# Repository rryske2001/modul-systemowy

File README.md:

# Moduł Systemowy HD44780 LCD Driver & PCB Adapter Collection

## 📖 O projekcie

Niniejsze repozytorium zawiera kompleksowe rozwiązanie dla obsługi popularnych wyświetlaczy znakowych LCD opartych na sterowniku **HD44780**. Projekt składa się z dwóch głównych filarów:
1.  **Warstwa sprzętowa:** Projekty płytek drukowanych (PCB) wykonane w środowisku **KiCad**, służące jako adaptery i moduły interfejsowe dla wyświetlaczy 16x2, 20x4 oraz 40x2.
2.  **Warstwa programowa:** Biblioteki sterowników napisane w języku C, obsługujące różne tryby komunikacji (I2C, 4-bit, 8-bit) ze szczególnym naciskiem na optymalizację (odczyt flagi zajętości - Busy Flag).

---

## 🛠️ Funkcjonalności

### 🔌 Hardware (Projekty PCB)
Projekty płytek zostały przygotowane w programie **KiCad**. Repozytorium zawiera pliki produkcyjne oraz źródłowe dla kilku wariantów:
* **Wersje jedno- i dwuwarstwowe:** Dostosowane do różnych metod produkcji (domowe trawienie vs profesjonalna produkcja).
* **Uniwersalność:** Obsługa popularnych formatów wyświetlaczy: 16x2, 20x4 oraz 40x2.
* **Adaptery I2C:** Projekty integrujące ekspandery portów (np. PCF8574) bezpośrednio z wyświetlaczem, co redukuje liczbę wymaganych pinów mikrokontrolera.

### 💻 Software (Sterowniki)
Kod źródłowy zawiera implementację sterowników w różnych konfiguracjach sprzętowych:
* **Obsługa I2C:** Sterowanie poprzez ekspander (PCF8574), idealne dla systemów z ograniczoną liczbą GPIO.
* **Tryb równoległy (4-bit i 8-bit):** Klasyczne sterowanie bezpośrednie.
* **Busy Flag Check:** Zaimplementowany mechanizm odczytu flagi zajętości sterownika HD44780. Pozwala to na uniknięcie sztywnych opóźnień (`delay`), co znacząco zwiększa wydajność całego systemu wbudowanego.
* **Interfejs szeregowy:** Alternatywne metody komunikacji.

---

## 📂 Struktura Repozytorium

Poniżej znajduje się opis zawartości kluczowych katalogów:

### Projekty KiCad
* `/Wersja_z_I2C_8bit_...` - Projekt dwuwarstwowej płytki z integracją I2C.
* `/Wersja_16x2_20x4_...` - Uniwersalna płytka jednowarstwowa dla standardowych wyświetlaczy.
* `/wersja_ostateczna_wyswietlacz_pcf_v1` - Finalna wersja adaptera z układem PCF.

### Kod Źródłowy
* `/wyswietlacz_interfejs_4_bit_BusyFlag` - Sterownik 4-bitowy z odczytem BF.
* `/testy_z_ekspanderem_pcf` - Kod testowy dla komunikacji I2C.
* `/wyswietlacz_interfejs_8_bit` - Podstawowa obsługa w trybie 8-bitowym.

---

## 🔧 Technologie i Narzędzia

* **Projektowanie PCB:** KiCad EDA
* **Język programowania:** C (Embedded)
* **Hardware:** Wyświetlacze HD44780, Ekspandery PCF8574
* **Protokoły:** I2C, Parallel Interface

---

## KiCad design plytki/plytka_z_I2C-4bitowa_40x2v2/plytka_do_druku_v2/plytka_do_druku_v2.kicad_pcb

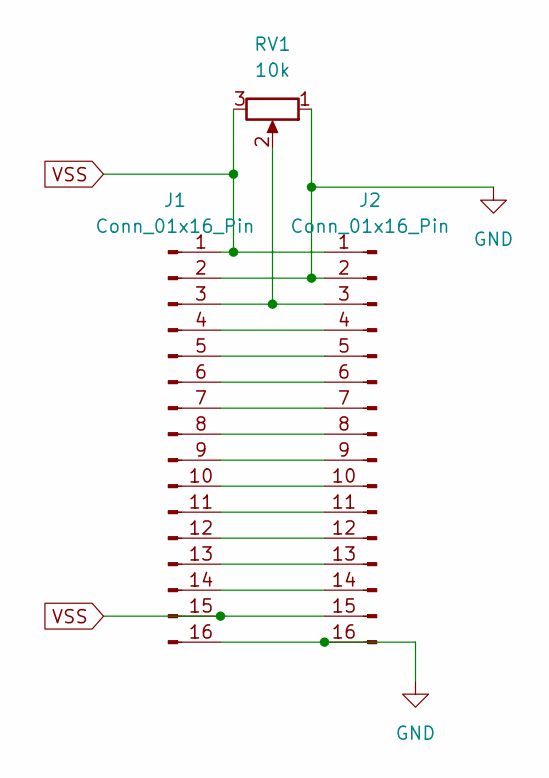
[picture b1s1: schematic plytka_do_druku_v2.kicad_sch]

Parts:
J1: Conn_01x16_Pin; PinSocket_1x16_P2.54mm_Vertical
J2: Conn_01x16_Pin; waski
RV1: 10k; Potentiometer_Alps_RK09Y11_Single_Horizontal

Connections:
GND: J1.2, J1.16, J2.2, J2.16, RV1.1
unnamed: J1.3, J2.3, RV1.2
unnamed: J1.4, J2.4
unnamed: J1.5, J2.5
unnamed: J1.6, J2.6
unnamed: J1.7, J2.7
unnamed: J1.8, J2.8
unnamed: J1.9, J2.9
unnamed: J1.10, J2.10
unnamed: J1.11, J2.11
unnamed: J1.12, J2.12
unnamed: J1.13, J2.13
unnamed: J1.14, J2.14
VSS: J1.1, J1.15, J2.1, J2.15, RV1.3

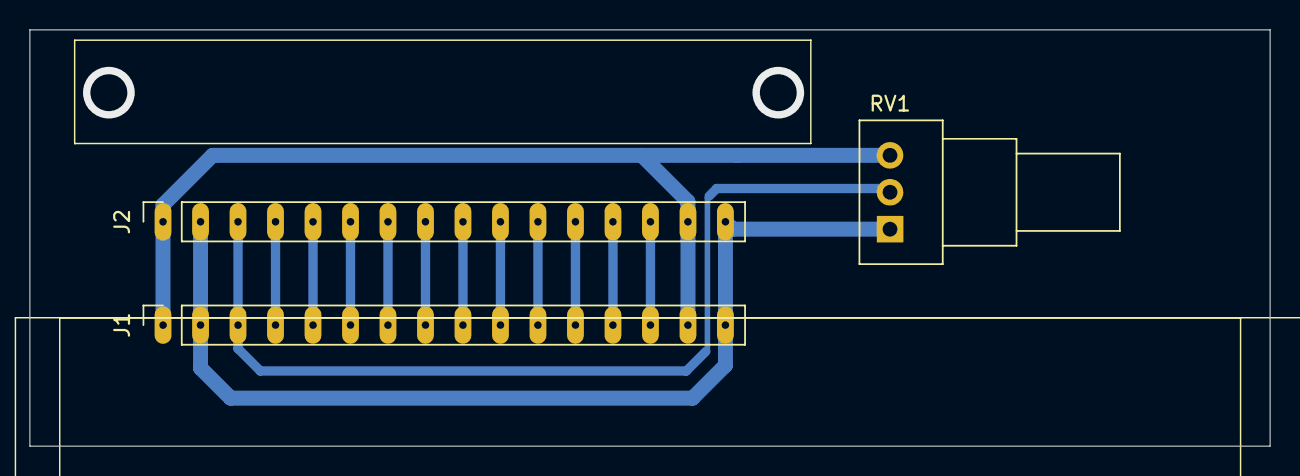
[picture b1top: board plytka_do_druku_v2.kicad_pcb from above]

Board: 2 copper layers, 84.0 x 28.2 mm, 3 parts (0 on the bottom side), 14 nets.

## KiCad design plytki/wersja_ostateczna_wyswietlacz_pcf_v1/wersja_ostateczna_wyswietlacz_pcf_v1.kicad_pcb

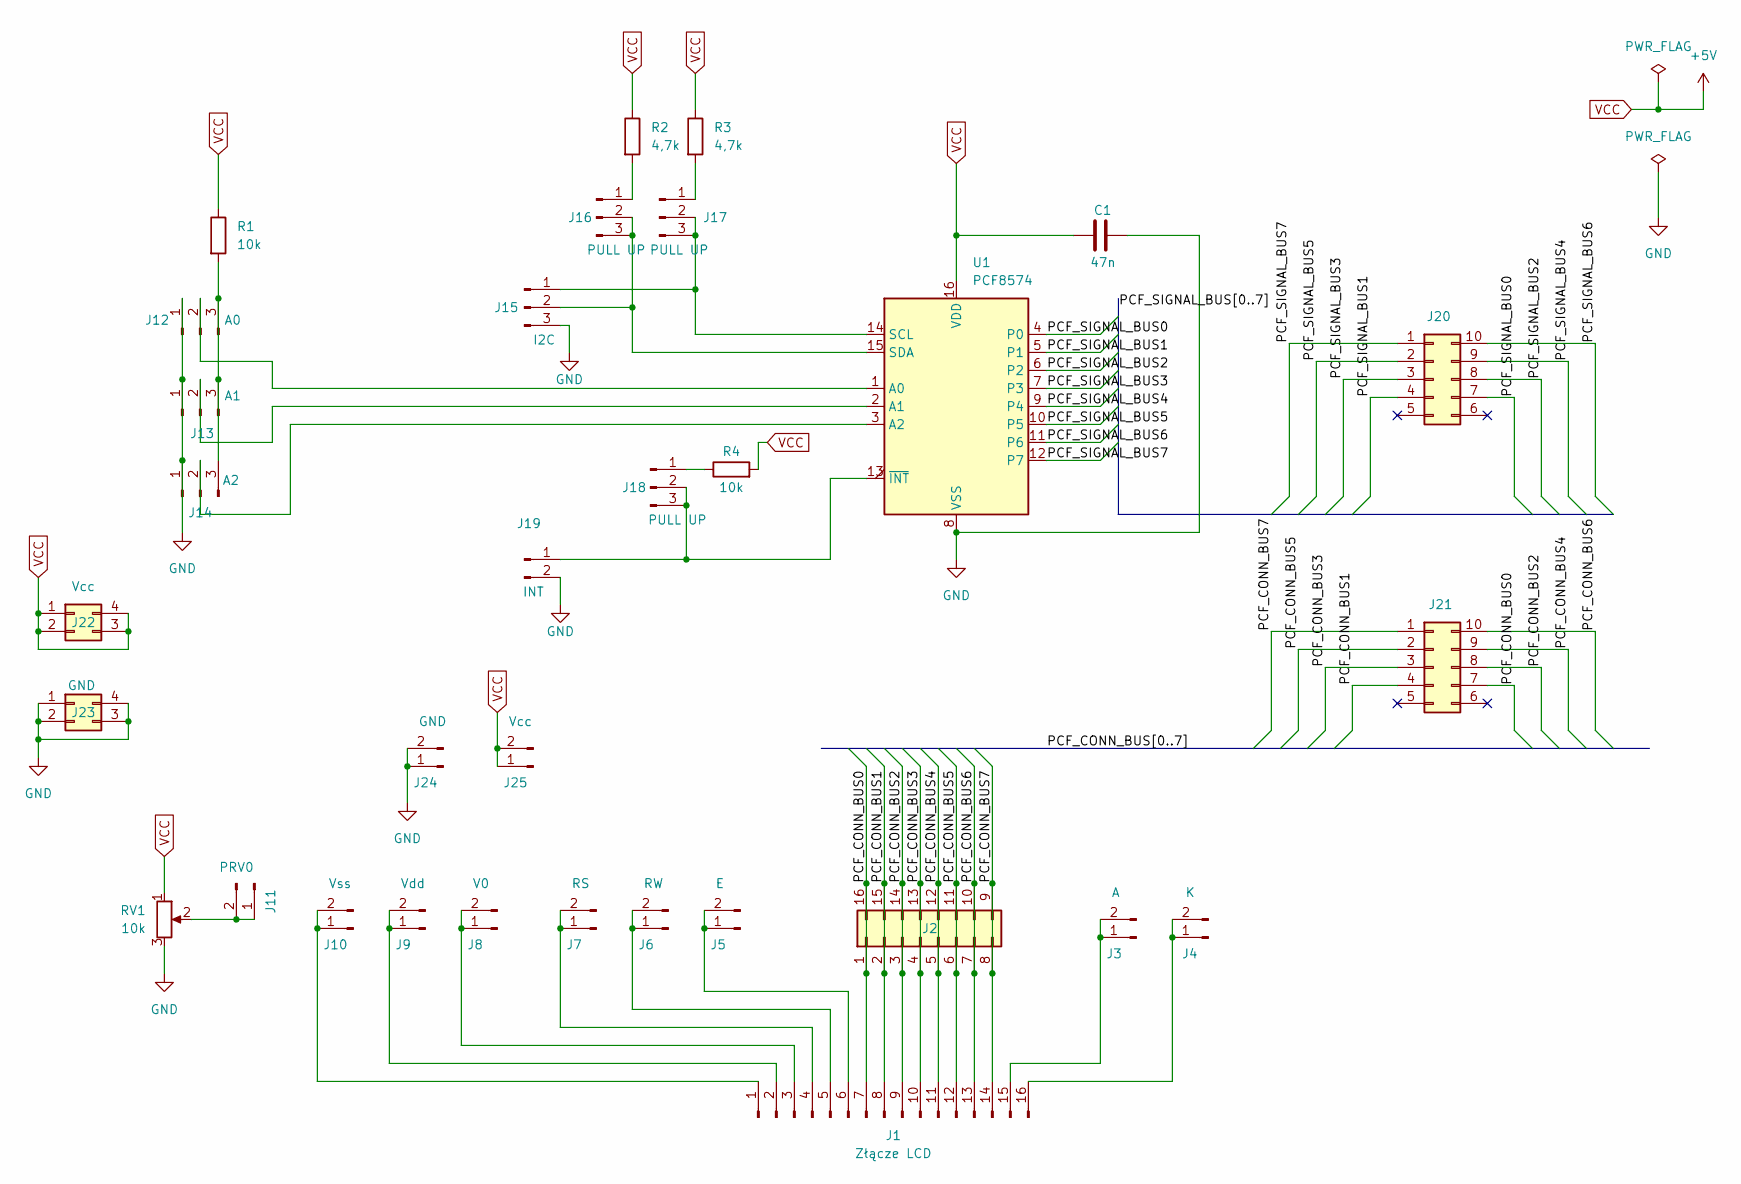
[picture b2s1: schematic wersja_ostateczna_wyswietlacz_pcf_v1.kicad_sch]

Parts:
C1: 47n; C_Disc_D8.0mm_W2.5mm_P5.00mm
J1: Złącze LCD; PinSocket_1x16_P2.54mm_Vertical
J2: Conn_02x08_Counter_Clockwise; PinSocket_2x08_P2.54mm_Vertical
J3: A; PinSocket_1x02_P2.54mm_Vertical_square
J4: K; PinSocket_1x02_P2.54mm_Vertical_square
J5: E; PinSocket_1x02_P2.54mm_Vertical_square
J6: RW; PinSocket_1x02_P2.54mm_Vertical_square
J7: RS; PinSocket_1x02_P2.54mm_Vertical_square
J8: V0; PinSocket_1x02_P2.54mm_Vertical_square
J9: Vdd; PinSocket_1x02_P2.54mm_Vertical_square
J10: Vss; PinSocket_1x02_P2.54mm_Vertical_square
J11: PRV0; PinSocket_1x02_P2.54mm_Vertical_square
J12: A0; PinSocket_1x03_P2.54mm_Vertical
J13: A1; PinSocket_1x03_P2.54mm_Vertical
J14: A2; PinSocket_1x03_P2.54mm_Vertical
J15: I2C; PinSocket_1x03_P2.54mm_Vertical
J16, J17, J18: PULL UP; PinSocket_1x03_P2.54mm_Vertical
J19: INT; PinSocket_1x02_P2.54mm_Vertical
J20, J21: Conn_02x05_Counter_Clockwise; PinSocket_2x05_P2.54mm_Vertical_LEZKA
J22: Vcc; PinSocket_2x02_P2.54mm_Vertical
J23: GND; PinSocket_2x02_P2.54mm_Vertical
J24: GND; PinSocket_1x02_P2.54mm_Vertical_square
J25: Vcc; PinSocket_1x02_P2.54mm_Vertical_square
R1, R4: 10k; R_Axial_DIN0207_L6.3mm_D2.5mm_P10.16mm_Horizontal_square
R2, R3: 4,7k; R_Axial_DIN0207_L6.3mm_D2.5mm_P10.16mm_Horizontal_square
RV1: 10k; Potentiometer_ACP_CA9-H5_Horizontal
U1: PCF8574; DIP-16_W7.62mm_Socket_LongPads

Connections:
/PCF_CONN_BUS0: J1.7, J2.1, J2.16, J21.7
/PCF_CONN_BUS1: J1.8, J2.2, J2.15, J21.4
/PCF_CONN_BUS2: J1.9, J2.3, J2.14, J21.8
/PCF_CONN_BUS3: J1.10, J2.4, J2.13, J21.3
/PCF_CONN_BUS4: J1.11, J2.5, J2.12, J21.9
/PCF_CONN_BUS5: J1.12, J2.6, J2.11, J21.2
/PCF_CONN_BUS6: J1.13, J2.7, J2.10, J21.10
/PCF_CONN_BUS7: J1.14, J2.8, J2.9, J21.1
/PCF_SIGNAL_BUS0: J20.7, U1.4 (P0)
/PCF_SIGNAL_BUS1: J20.4, U1.5 (P1)
/PCF_SIGNAL_BUS2: J20.8, U1.6 (P2)
/PCF_SIGNAL_BUS3: J20.3, U1.7 (P3)
/PCF_SIGNAL_BUS4: J20.9, U1.9 (P4)
/PCF_SIGNAL_BUS5: J20.2, U1.10 (P5)
/PCF_SIGNAL_BUS6: J20.10, U1.11 (P6)
/PCF_SIGNAL_BUS7: J20.1, U1.12 (P7)
GND: C1.1, J12.1, J13.1, J14.1, J15.3, J19.2, J23.1, J23.2, J23.3, J23.4, J24.1, J24.2, RV1.3, U1.8 (VSS)
unnamed: J1.1, J10.1, J10.2
unnamed: J1.2, J9.1, J9.2
unnamed: J1.3, J8.1, J8.2
unnamed: J1.4, J7.1, J7.2
unnamed: J1.5, J6.1, J6.2
unnamed: J1.6, J5.1, J5.2
unnamed: J1.15, J3.1, J3.2
unnamed: J1.16, J4.1, J4.2
unnamed: J11.1, J11.2, RV1.2
unnamed: J12.2, U1.1 (A0)
unnamed: J12.3, J13.3, J14.3, R1.2
unnamed: J13.2, U1.2 (A1)
unnamed: J14.2, U1.3 (A2)
unnamed: J15.1, J17.2, J17.3, U1.14 (SCL)
unnamed: J15.2, J16.2, J16.3, U1.15 (SDA)
unnamed: J16.1, R2.2
unnamed: J17.1, R3.2
unnamed: J18.1, R4.1
unnamed: J18.2, J18.3, J19.1, U1.13 (~INT)
VCC: C1.2, J22.1, J22.2, J22.3, J22.4, J25.1, J25.2, R1.1, R2.1, R3.1, R4.2, RV1.1, U1.16 (VDD)

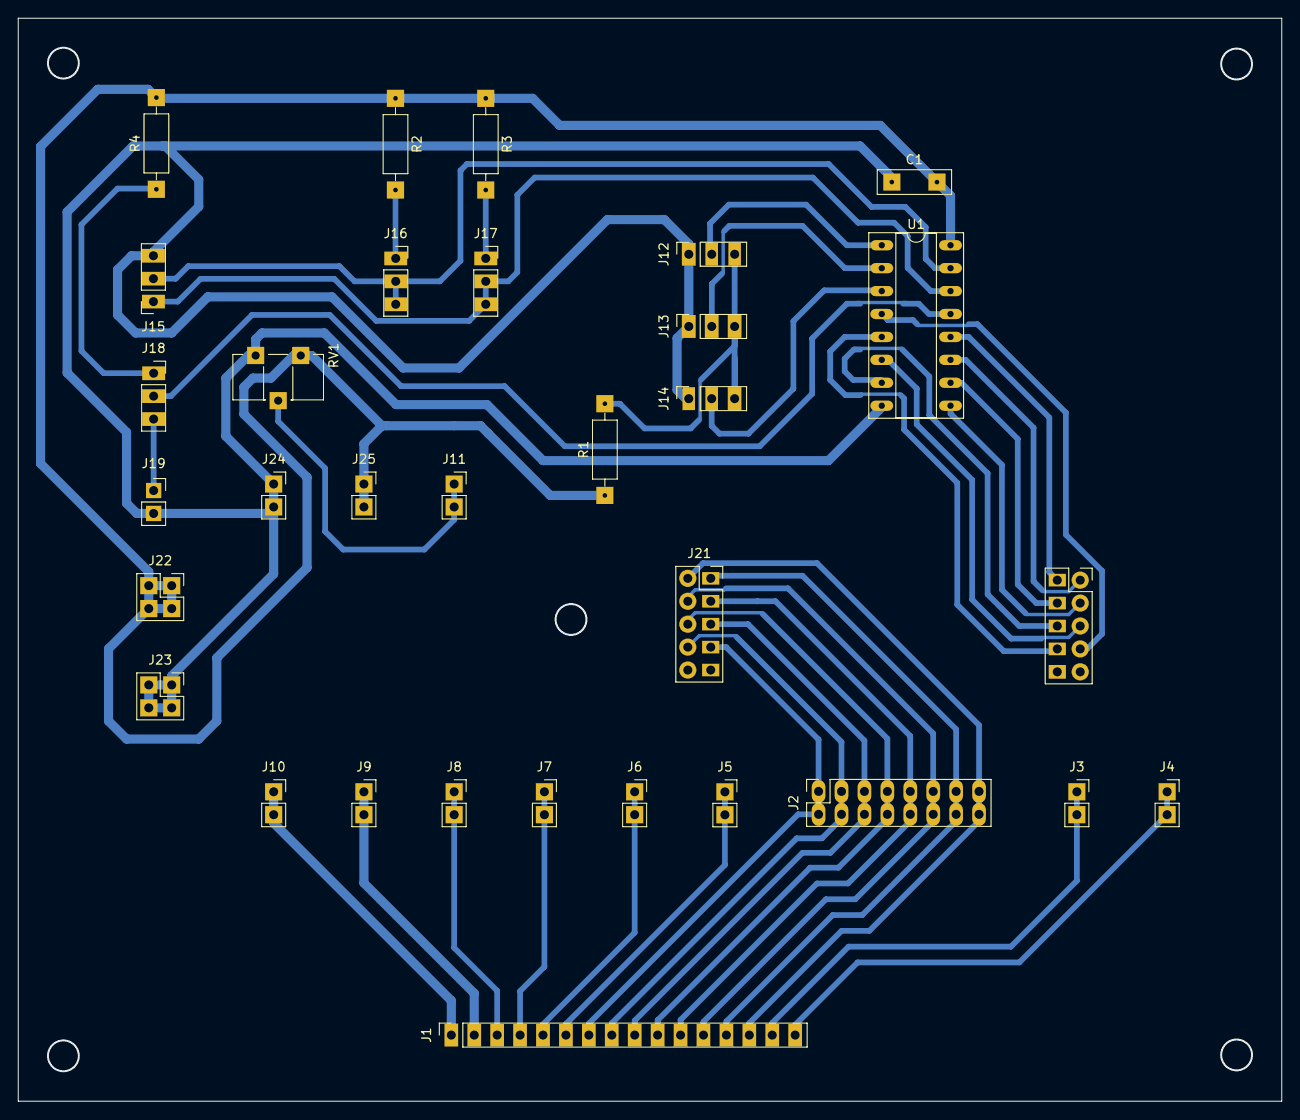
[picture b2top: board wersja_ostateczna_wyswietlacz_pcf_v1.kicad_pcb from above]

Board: 2 copper layers, 140.0 x 120.0 mm, 32 parts (0 on the bottom side), 37 nets.

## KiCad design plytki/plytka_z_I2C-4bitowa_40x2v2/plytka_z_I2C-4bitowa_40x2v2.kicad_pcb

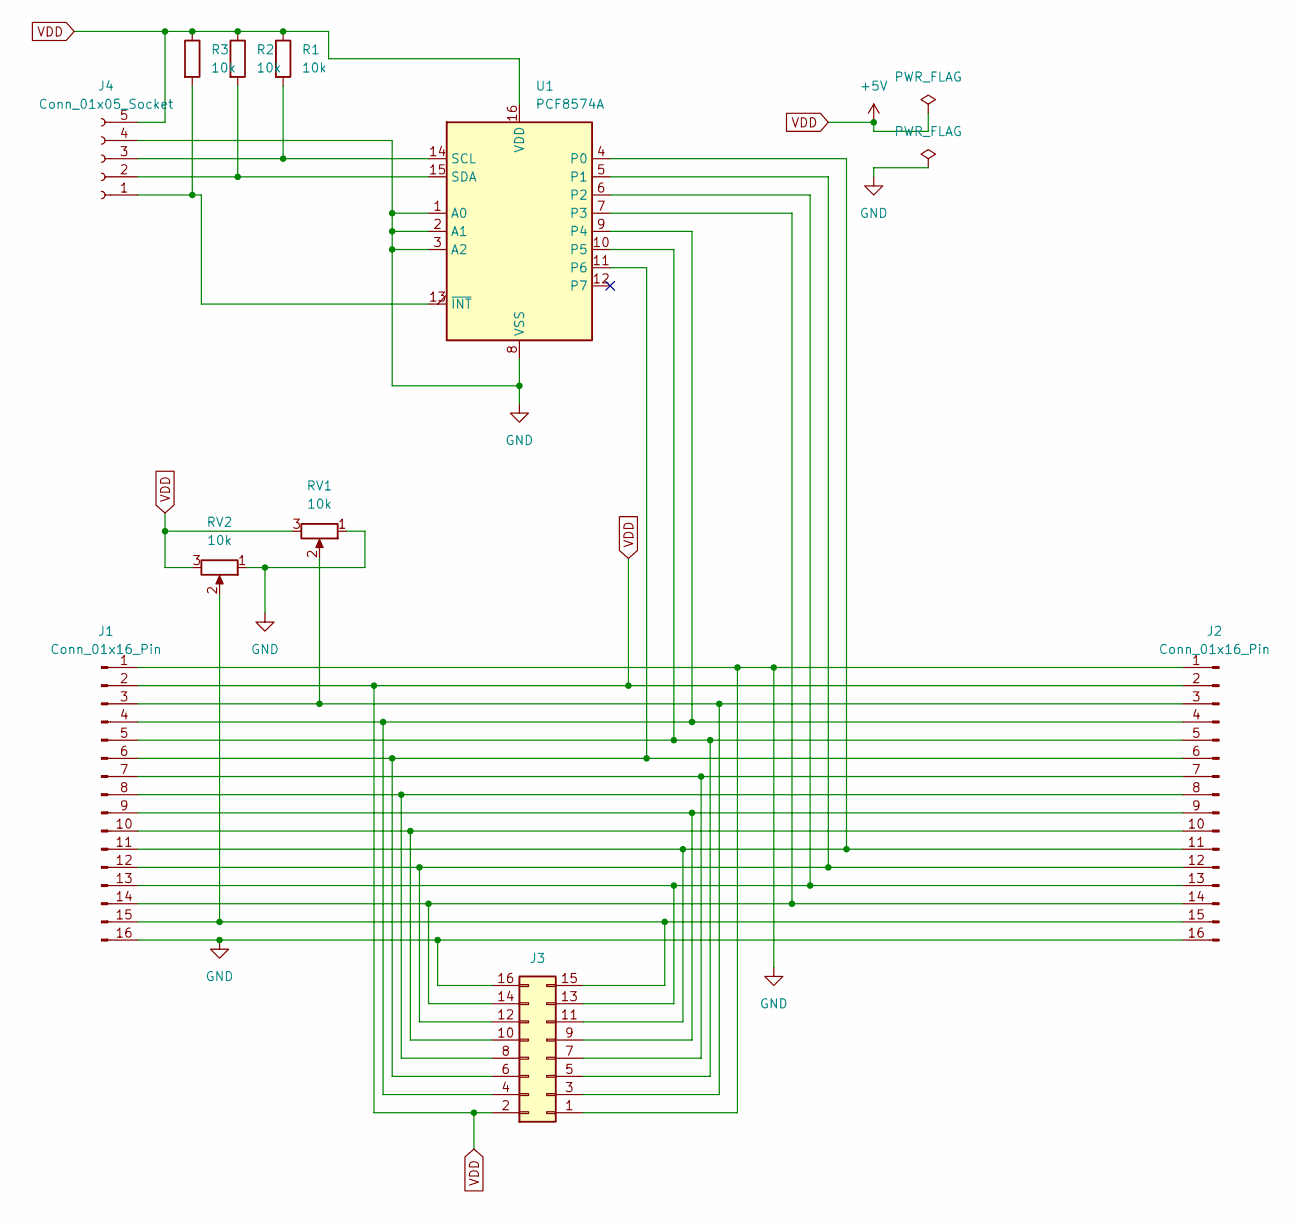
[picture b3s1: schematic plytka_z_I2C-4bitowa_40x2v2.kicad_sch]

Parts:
J1, J2: Conn_01x16_Pin; PinSocket_1x16_P2.54mm_Vertical
J3: Conn_02x08_Odd_Even; PinSocket_2x08_P2.54mm_Vertical
J4: Conn_01x05_Socket; PinSocket_1x05_P2.54mm_Vertical
R1, R2, R3: 10k; R_Axial_DIN0204_L3.6mm_D1.6mm_P5.08mm_Horizontal
RV1, RV2: 10k; Potentiometer_ACP_CA6-H2,5_Horizontal
U1: PCF8574A; DIP-16_W7.62mm_Socket

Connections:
GND: J1.1, J1.16, J2.1, J2.16, J3.1, J3.16, J4.4 (Pin_SDA), RV1.1, RV2.1, U1.1 (A0), U1.2 (A1), U1.3 (A2), U1.8 (VSS)
unnamed: J1.3, J2.3, J3.3, RV1.2
unnamed: J1.4, J2.4, J3.4, U1.9 (P4)
unnamed: J1.5, J2.5, J3.5, U1.10 (P5)
unnamed: J1.6, J2.6, J3.6, U1.11 (P6)
unnamed: J1.7, J2.7, J3.7
unnamed: J1.8, J2.8, J3.8
unnamed: J1.9, J2.9, J3.9
unnamed: J1.10, J2.10, J3.10
unnamed: J1.11, J2.11, J3.11, U1.4 (P0)
unnamed: J1.12, J2.12, J3.12, U1.5 (P1)
unnamed: J1.13, J2.13, J3.13, U1.6 (P2)
unnamed: J1.14, J2.14, J3.14, U1.7 (P3)
unnamed: J1.15, J2.15, J3.15, RV2.2
unnamed: J4.2 (Pin_GND), R2.2, U1.15 (SDA)
unnamed: J4.3 (Pin_SCL), R1.2, U1.14 (SCL)
unnamed: J4.1 (Pin_VDD), R3.2, U1.13 (~INT)
VDD: J1.2, J2.2, J3.2, J4.5 (Pin_INT), R1.1, R2.1, R3.1, RV1.3, RV2.3, U1.16 (VDD)

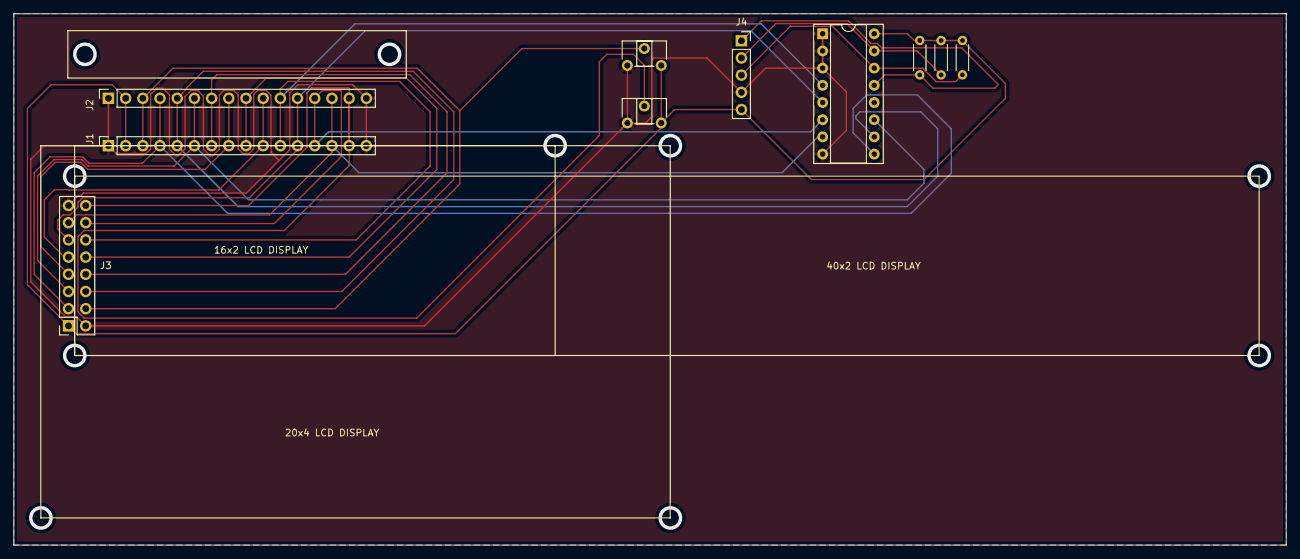
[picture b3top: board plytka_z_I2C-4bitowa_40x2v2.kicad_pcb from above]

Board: 2 copper layers, 188.0 x 78.5 mm, 10 parts (0 on the bottom side), 18 nets.

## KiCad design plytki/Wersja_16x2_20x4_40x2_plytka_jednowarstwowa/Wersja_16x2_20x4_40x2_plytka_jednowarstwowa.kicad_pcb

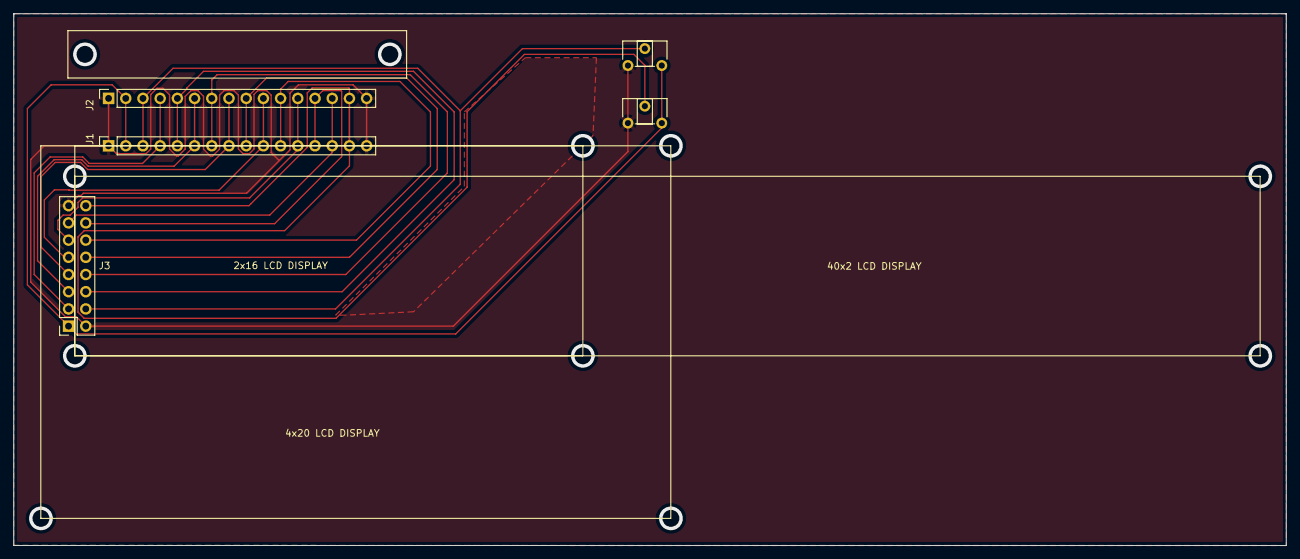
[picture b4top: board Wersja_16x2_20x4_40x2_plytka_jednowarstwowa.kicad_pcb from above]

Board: 2 copper layers, 187.9 x 78.5 mm, 5 parts (0 on the bottom side), 15 nets.

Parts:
J1, J2: Conn_01x16_Pin; PinSocket_1x16_P2.54mm_Vertical
J3: Conn_02x08_Odd_Even; PinSocket_2x08_P2.54mm_Vertical
RV1, RV2: 10k; Potentiometer_ACP_CA6-H2,5_Horizontal

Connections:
GND: J1.1, J1.16, J2.1, J2.16, J3.1, J3.16, RV1.1, RV2.1
unnamed: J1.3, J2.3, J3.3, RV1.2
unnamed: J1.4, J2.4, J3.4
unnamed: J1.5, J2.5, J3.5
unnamed: J1.6, J2.6, J3.6
unnamed: J1.7, J2.7, J3.7
unnamed: J1.8, J2.8, J3.8
unnamed: J1.9, J2.9, J3.9
unnamed: J1.10, J2.10, J3.10
unnamed: J1.11, J2.11, J3.11
unnamed: J1.12, J2.12, J3.12
unnamed: J1.13, J2.13, J3.13
unnamed: J1.14, J2.14, J3.14
unnamed: J1.15, J2.15, J3.15, RV2.2
VDD: J1.2, J2.2, J3.2, RV1.3, RV2.3

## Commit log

2026-01-13 Commit kodow oraz plytek
2026-01-13 Dodany opis README
2026-03-15 Update README
    Removed a sentence about demonstrating embedded system design skills.
